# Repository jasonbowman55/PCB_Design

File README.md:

# PCB_Design

This repository will hold all of the necessary files for me to begin learning how to better design PCB boards, as well as project files for various PCB design projects.

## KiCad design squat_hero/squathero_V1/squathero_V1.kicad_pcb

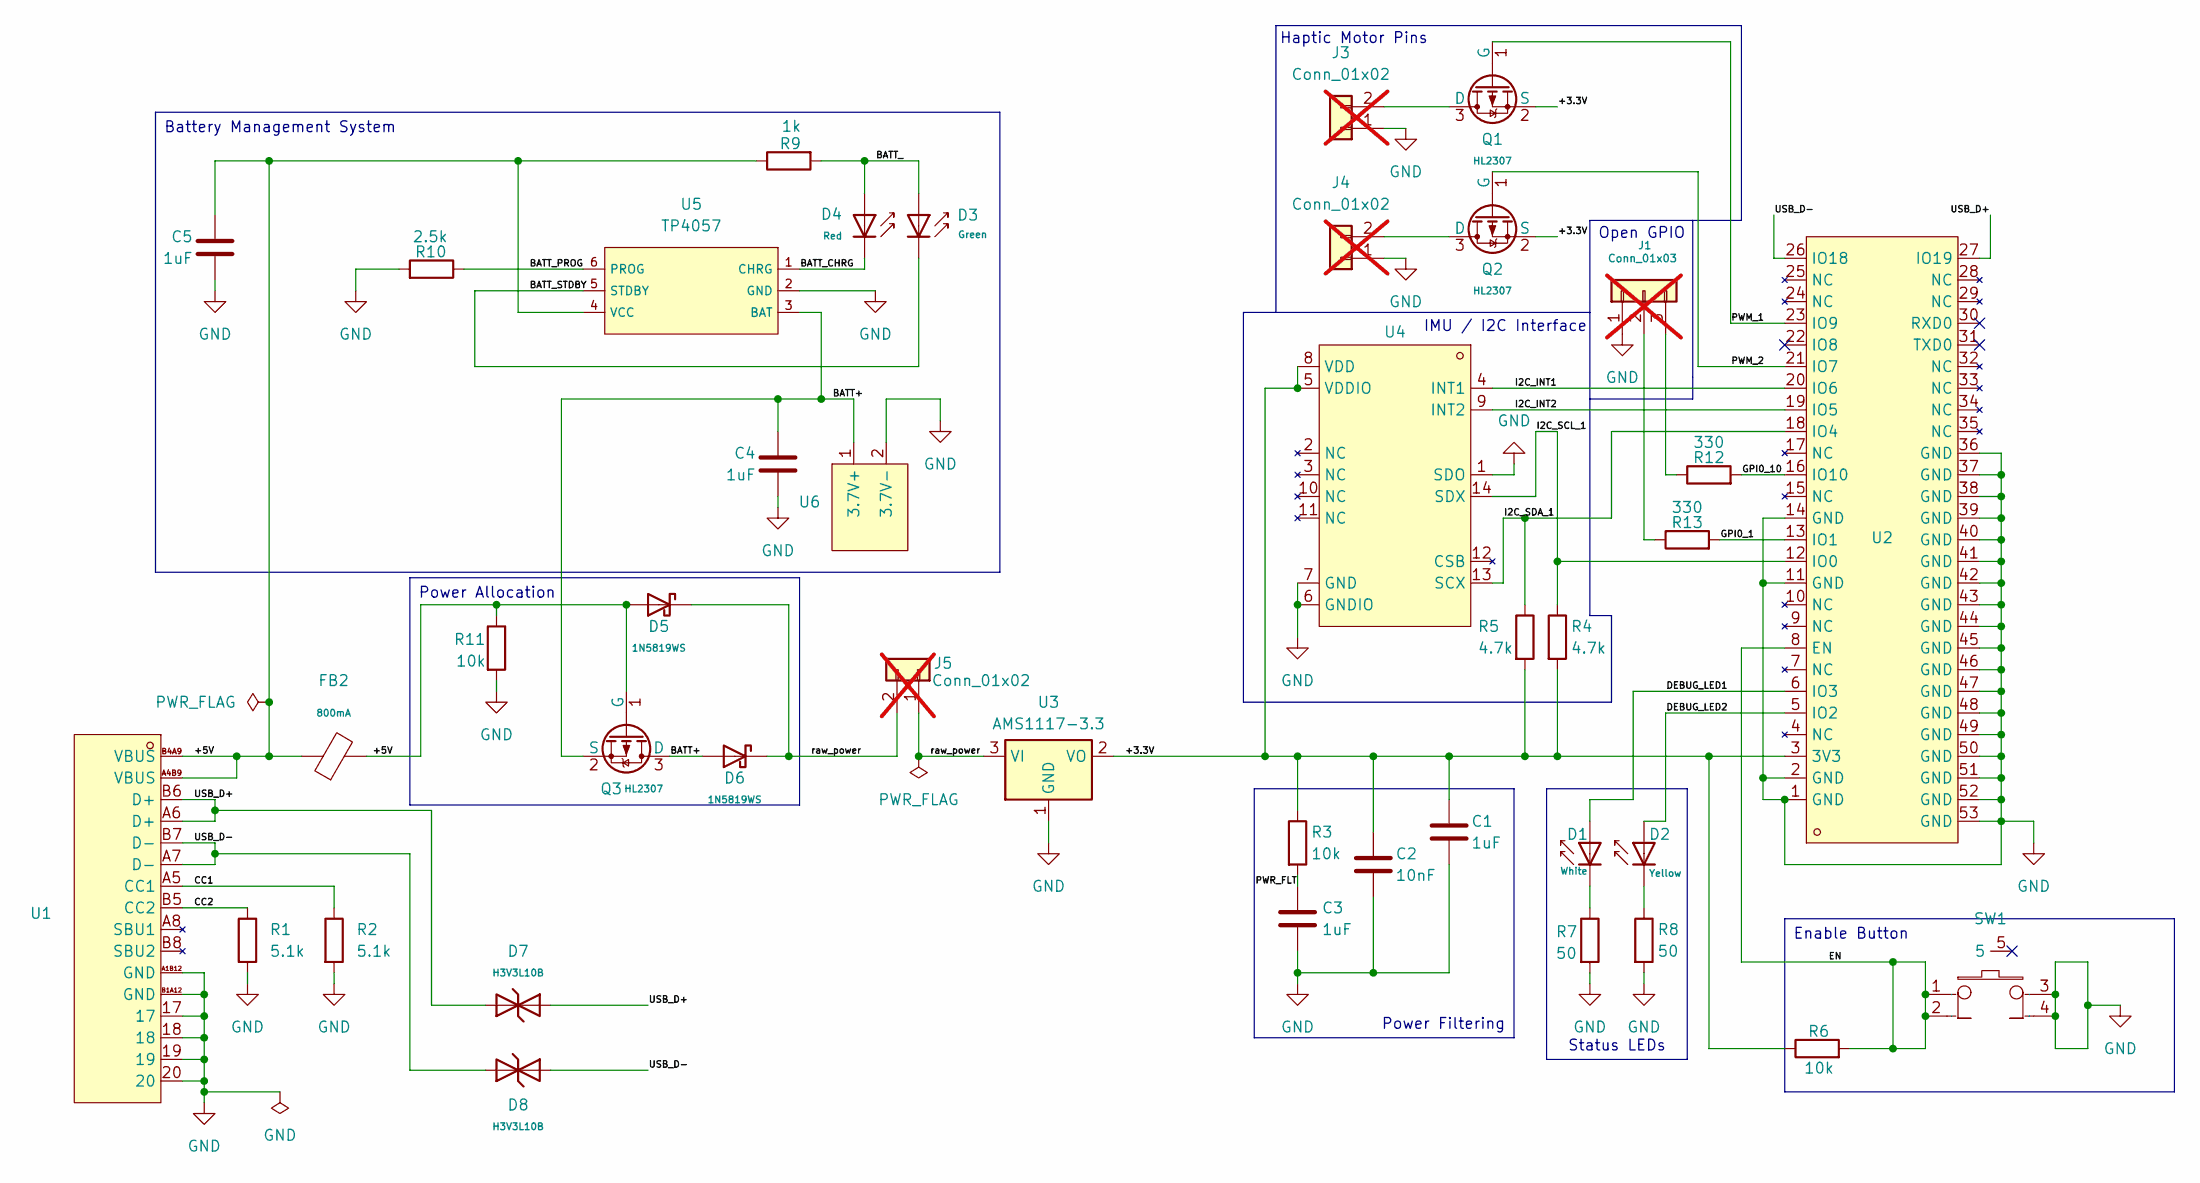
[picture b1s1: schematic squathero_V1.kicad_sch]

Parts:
C1, C3, C4, C5: 1uF; R_0805_2012Metric
C2: 10nF; R_0805_2012Metric
D1: White; D_0805; Part KT-0805W; LCSC C34499
D2: Yellow; D_0805; Part KT-0805Y; LCSC C2296
D3: Green; D_0805; Part KT-0805G; LCSC C2297
D4: Red; D_0603; Part KT-0603R; LCSC C2286
D5, D6: 1N5819WS; D_SOD-323; Forward Voltage (Vf@If) 600mV@1A; Reverse Voltage (Vr) 40V; Part 1N5819WS; LCSC C191023
D7, D8: H3V3L10B; D_DFN1006-2L; Breakdown Voltage 5.5V; Part H3V3L10B; LCSC C20615781
FB2: FB_0805; Current Rating 800mA; Tolerance ±25%; Part GZ2012D101TF; LCSC C1015
J1: Conn_01x03; PinSocket_1x03_P2.54mm_Vertical; not fitted
J3, J4, J5: Conn_01x02; PinSocket_1x02_P2.54mm_Vertical; not fitted
Q1, Q2, Q3: HL2307; Q_SOT-23; Part HL2307; LCSC C28646274
R1, R2: 5.1k; R_0603_1608Metric
R3, R6, R11: 10k; R_0805_2012Metric
R4, R5: 4.7k; R_0805_2012Metric
R7, R8: 50; R_0805_2012Metric
R9: 1k; R_0805_2012Metric
R10: 2.5k; R_0805_2012Metric
R12, R13: 330; R_0805_2012Metric
SW1: SW-SMD_4P-L3.5-W3.5_PTS840GKPSMTRLFS; Manufacturer Part PTS840GKPSMTRLFS; LCSC Part Name 轻触开关3.5mm*3.55mm，220gf
U1: USB-SMD_TYPE-C16PIN-1; Manufacturer Part 12402012E212A; LCSC Part Name Type-C 母
U2: WIFIM-SMD_ESP32-C3-MINI-1; Manufacturer Part ESP32-C3-MINI-1-N4; LCSC Part Name ESP32-C3-MINI-1-N4
U3: AMS1117-3.3; SOT-223-3_TabPin2
U4: LGA-14_L3.0-W2.5-P0.50-TL_QMI8658A; Manufacturer Part BMI323; LCSC Part Name BMI323
U5: TP4057; SOT-23-6_L2.9-W1.6-P0.95-LS2.8-BL; Part TP4057-42-SOT26-R; LCSC C12044
U6: Untitled

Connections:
/+3.3V: C1.1, C2.1, Q1.2 (S), Q2.2 (S), R3.1, R4.2, R5.2, R6.1, U2.3 (3V3), U3.2 (VO), U4.5 (VDDIO), U4.8 (VDD)
/+5V: C5.1, D5.2, FB2.1, FB2.2, Q3.1 (G), R9.1, R11.1, U1.A4B9 (VBUS), U1.B4A9 (VBUS), U5.4 (VCC)
/BATT+: C4.1, D6.2, Q3.2 (S), Q3.3 (D), U5.3 (BAT), U6.1 (3.7V+)
/BATT_: D3.2, D4.2, R9.2
/BATT_CHRG: D4.1, U5.1 (CHRG)
/BATT_PROG: R10.1, U5.6 (PROG)
/BATT_STDBY: D3.1, U5.5 (STDBY)
/CC1: R2.1, U1.A5 (CC1)
/CC2: R1.1, U1.B5 (CC2)
/DEBUG_LED1: D1.2, U2.6 (IO3)
/DEBUG_LED2: D2.2, U2.5 (IO2)
/EN: R6.2, SW1.1, SW1.2, U2.8 (EN)
/GPI0_1: R13.2, U2.13 (IO1)
/GPI0_10: R12.2, U2.16 (IO10)
/I2C_INT1: U2.20 (IO6), U4.4 (INT1)
/I2C_INT2: U2.19 (IO5), U4.9 (INT2)
/I2C_SCL_1: R4.1, U2.12 (IO0), U4.14 (SDX)
/I2C_SDA_1: R5.1, U2.18 (IO4), U4.13 (SCX)
/PWM_1: Q1.1 (G), U2.23 (IO9)
/PWM_2: Q2.1 (G), U2.21 (IO7)
/PWR_FLT: C3.1, R3.2
/USB_D+: D7.1, D7.2, U1.A6 (D+), U1.B6 (D+), U2.27 (IO19)
/USB_D-: D8.1, D8.2, U1.A7 (D-), U1.B7 (D-), U2.26 (IO18)
/raw_power: D5.1, D6.1, J5.1, J5.2, U3.3 (VI)
GND: C1.2, C2.2, C3.2, C4.2, C5.2, J1.1, J3.1, J4.1, R1.2, R2.2, R7.2, R8.2, R10.2, R11.2, SW1.3, SW1.4, U1.17, U1.18, U1.19, U1.20, U1.A1B12 (GND), U1.B1A12 (GND), U2.1 (GND), U2.2 (GND), U2.11 (GND), U2.14 (GND), U2.36 (GND), U2.37 (GND), U2.38 (GND), U2.39 (GND), U2.40 (GND), U2.41 (GND), U2.42 (GND), U2.43 (GND), U2.44 (GND), U2.45 (GND), U2.46 (GND), U2.47 (GND), U2.48 (GND), U2.49 (GND), U2.50 (GND), U2.51 (GND), U2.52 (GND), U2.53 (GND), U3.1 (GND), U4.1 (SDO), U4.6 (GNDIO), U4.7 (GND), U5.2 (GND), U6.2 (3.7V-)
unnamed: D1.1, R7.1
unnamed: D2.1, R8.1
unnamed: J1.2, R13.1
unnamed: J1.3, R12.1
unnamed: J3.2, Q1.3 (D)
unnamed: J4.2, Q2.3 (D)

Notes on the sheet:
Haptic Motor Pins
IMU / I2C Interface
Open GPIO
Battery Management System
Power Allocation
Power Filtering
Status LEDs
Enable Button

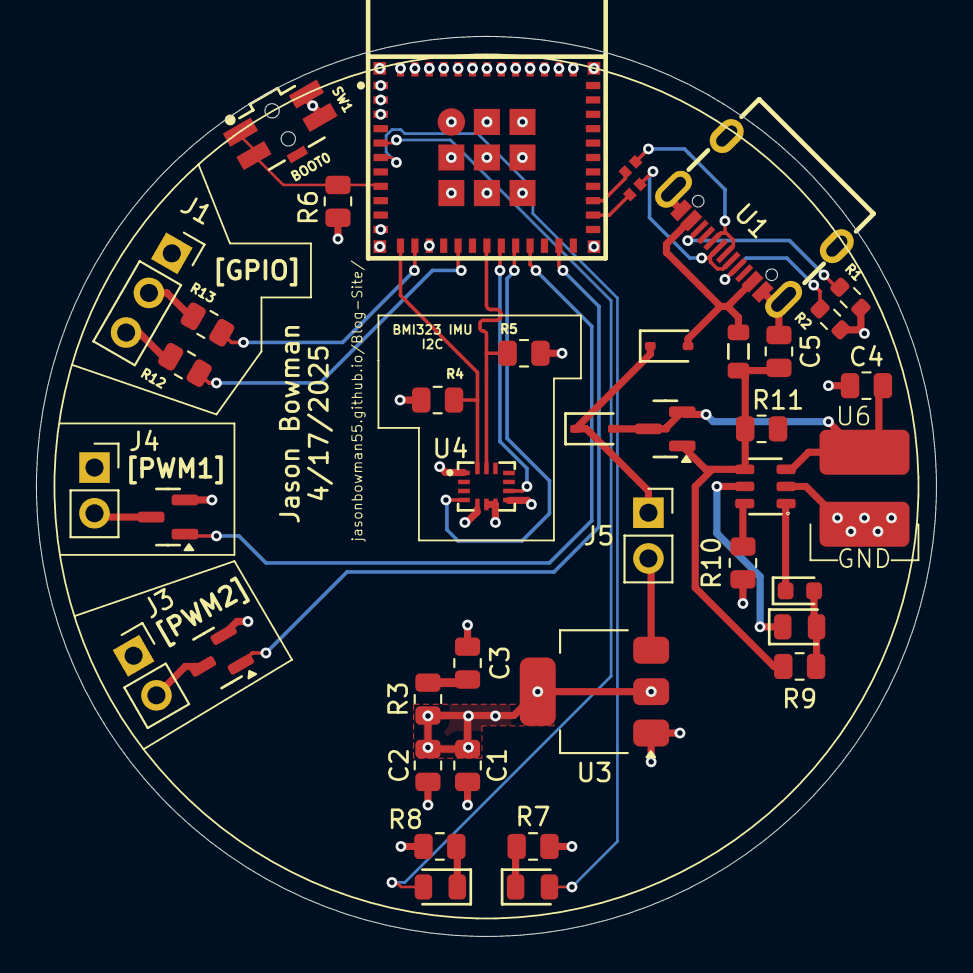
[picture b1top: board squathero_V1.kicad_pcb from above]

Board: 4 copper layers, 50.0 x 50.0 mm, 41 parts (0 on the bottom side), 31 nets.

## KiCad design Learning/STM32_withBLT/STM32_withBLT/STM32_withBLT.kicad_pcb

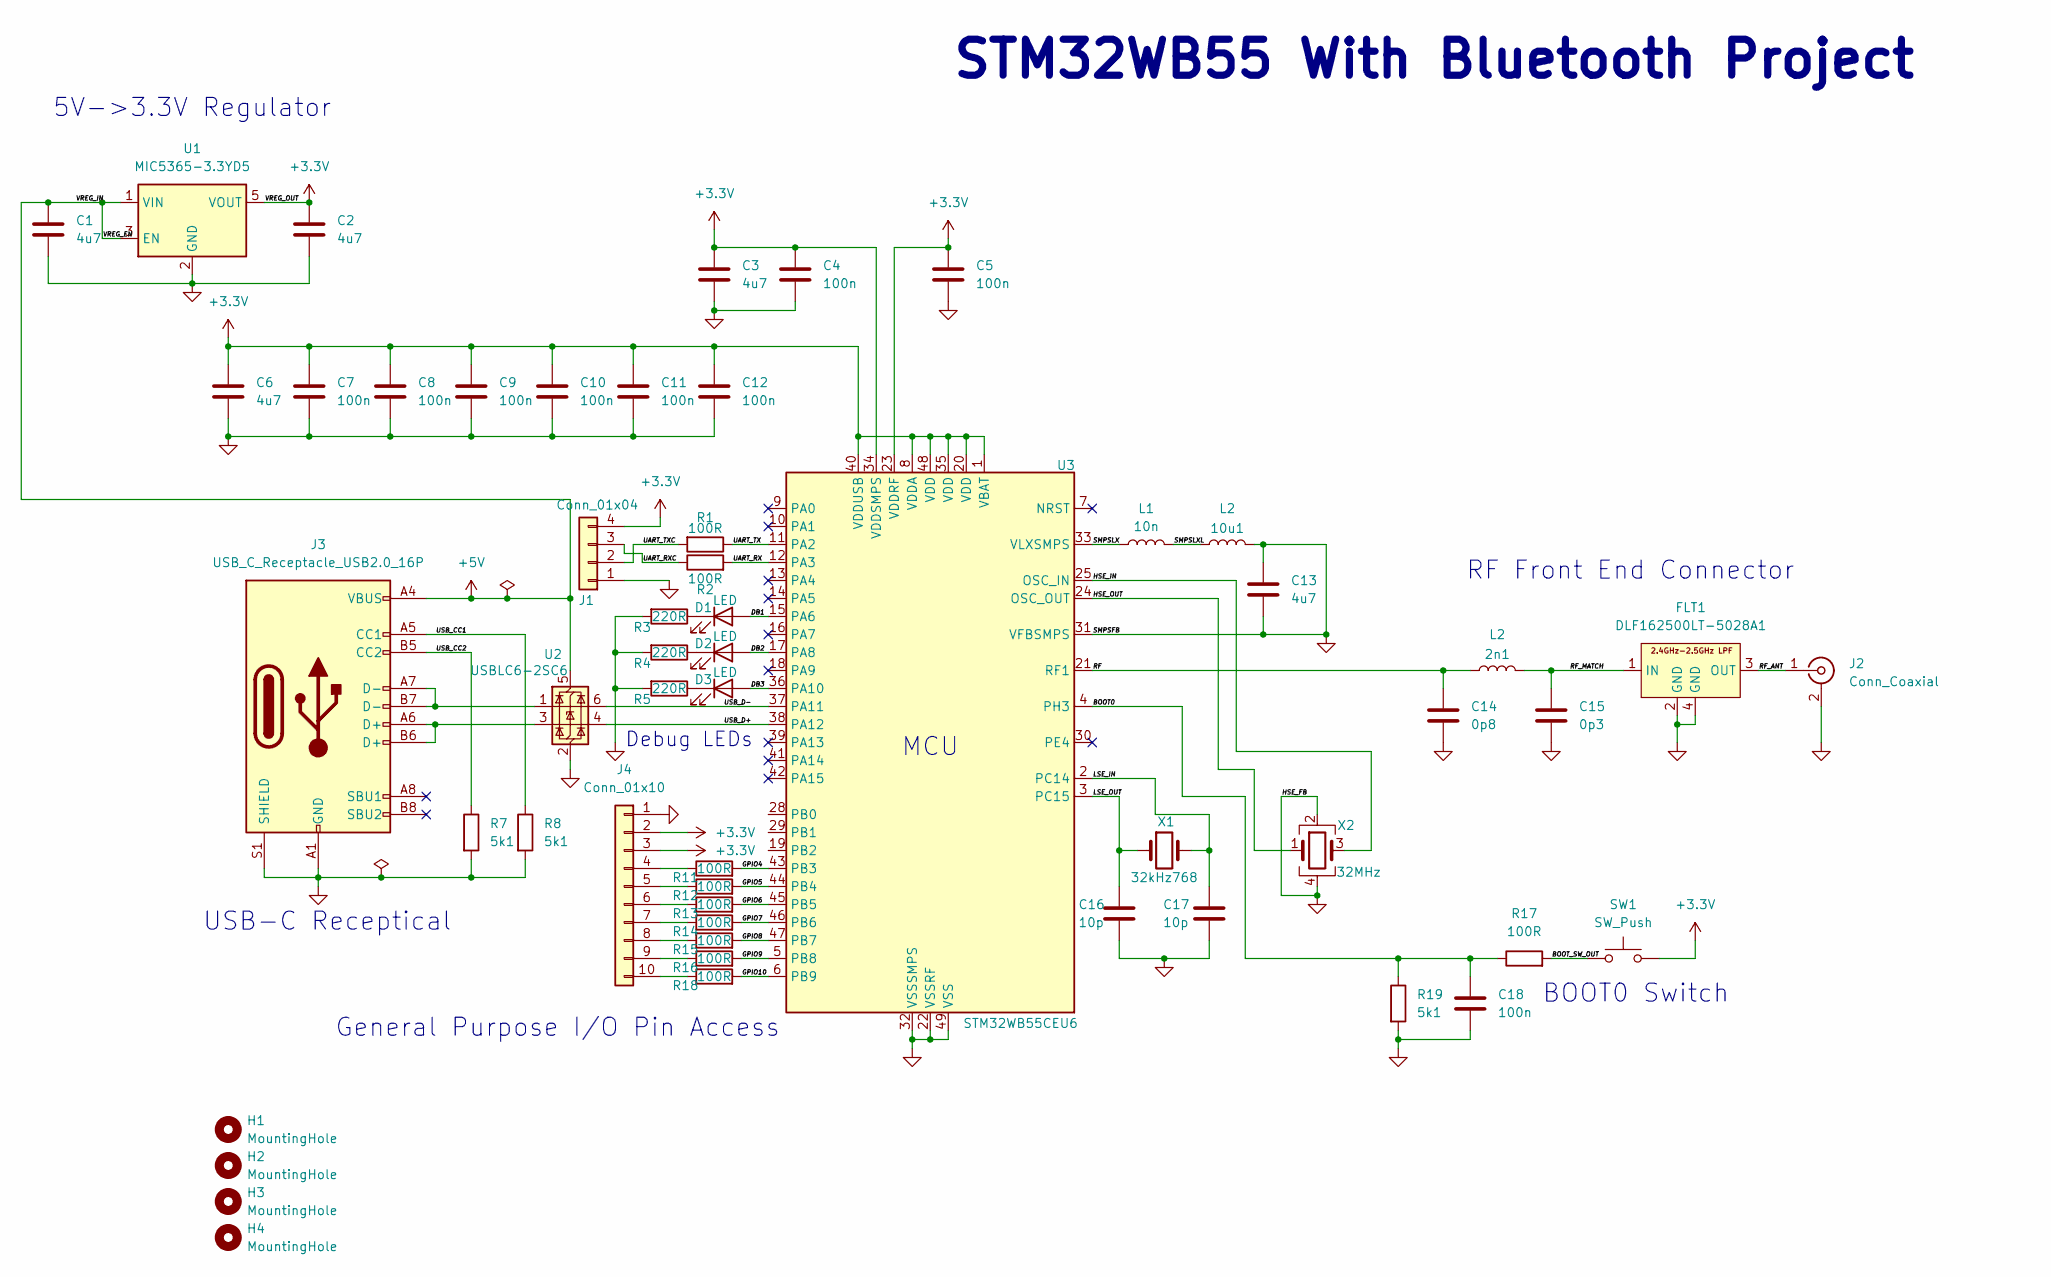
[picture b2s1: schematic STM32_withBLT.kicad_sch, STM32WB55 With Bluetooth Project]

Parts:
2n1: L2; C_0402_1005Metric
10u1: L2; C_0805_2012Metric
C1, C6: 4u7; C_0201_0603Metric
C2, C3, C13: 4u7; C_0402_1005Metric
C4, C5, C7, C8, C9, C10, C12, C18: 100n; C_0402_1005Metric
C11: 100n; C_0201_0603Metric
C14: 0p8; C_0402_1005Metric
C15: 0p3; C_0402_1005Metric
C16, C17: 10p; C_0402_1005Metric
D1, D2, D3: LED; C_0402_1005Metric
FLT1: DLF162500LT-5028A1
H1, H2, H3, H4: MountingHole; MountingHole_3.2mm_M3_Pad
J1: Conn_01x04; PinHeader_1x04_P2.54mm_Vertical
J2: Conn_Coaxial; U.FL_Hirose_U.FL-R-SMT-1_Vertical
J3: USB_C_Receptacle_USB2.0_16P; USB_C_Receptacle_GCT_USB4105-xx-A_16P_TopMnt_Horizontal
J4: Conn_01x10; PinHeader_1x10_P2.54mm_Vertical
L1: 10n; C_0402_1005Metric
R1, R2, R11, R12, R13, R14, R15, R16, R17, R18: 100R; C_0402_1005Metric
R3, R4, R5: 220R; C_0402_1005Metric
R7, R8, R19: 5k1; C_0402_1005Metric
SW1: SW_Push; SW_SPST_FSMSM
U1: MIC5365-3.3YD5; SOT-23-5
U2: USBLC6-2SC6; SOT-23-6
U3: STM32WB55CEU6; QFN-48-1EP_7x7mm_P0.5mm_EP5.6x5.6mm
X1: 32kHz768; Crystal_SMD_2012-2Pin_2.0x1.2mm
X2: 32MHz; Crystal_SMD_2016-4Pin_2.0x1.6mm

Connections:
+3.3V: C2.1, C3.1, C4.1, C5.1, C6.1, C7.1, C8.1, C9.1, C10.1, C11.1, C12.1, J1.4, J4.2, J4.3, SW1.2, U1.5 (VOUT), U3.1 (VBAT), U3.8 (VDDA), U3.20 (VDD), U3.23 (VDDRF), U3.34 (VDDSMPS), U3.35 (VDD), U3.40 (VDDUSB), U3.48 (VDD)
+5V: C1.1, J3.A4 (VBUS), J3.A9 (VBUS), J3.B4 (VBUS), J3.B9 (VBUS), U1.1 (VIN), U1.3 (EN), U2.5 (VBUS)
/BOOT0: C18.1, R17.1, R19.1, U3.4 (PH3)
/BOOT_SW_OUT: R17.2, SW1.1
/DB1: D1.2 (A), U3.15 (PA6)
/DB2: D2.2 (A), U3.17 (PA8)
/DB3: D3.2 (A), U3.36 (PA10)
/GPIO4: R11.2, U3.43 (PB3)
/GPIO5: R12.2, U3.44 (PB4)
/GPIO6: R13.2, U3.45 (PB5)
/GPIO7: R14.2, U3.46 (PB6)
/GPIO8: R15.2, U3.47 (PB7)
/GPIO9: R16.2, U3.5 (PB8)
/GPIO10: R18.2, U3.6 (PB9)
/HSE_IN: U3.25 (OSC_IN), X2.3
/HSE_OUT: U3.24 (OSC_OUT), X2.1
/LSE_IN: C17.1, U3.2 (PC14), X1.2
/LSE_OUT: C16.1, U3.3 (PC15), X1.1
/RF: 2n1.1, C14.1, U3.21 (RF1)
/RF_ANT: FLT1.3 (OUT), J2.1 (In)
/RF_MATCH: 2n1.2, C15.1, FLT1.1 (IN)
/SMPSLX: L1.1, U3.33 (VLXSMPS)
/SMPSLXL: 10u1.1, L1.2
/UART_RX: R2.2, U3.12 (PA3)
/UART_RXC: J1.3, R2.1
/UART_TX: R1.1, U3.11 (PA2)
/UART_TXC: J1.2, R1.2
/USB_CC1: J3.A5 (CC1), R8.1
/USB_CC2: J3.B5 (CC2), R7.1
/USB_D+: U2.4 (I/O2), U3.38 (PA12)
/USB_D-: U2.6 (I/O1), U3.37 (PA11)
GND: 10u1.2, C1.2, C2.2, C3.2, C4.2, C5.2, C6.2, C7.2, C8.2, C9.2, C10.2, C11.2, C12.2, C13.1, C13.2, C14.2, C15.2, C16.2, C17.2, C18.2, FLT1.2 (GND), FLT1.4 (GND), J1.1, J2.2 (Ext), J3.A1 (GND), J3.A12 (GND), J3.B1 (GND), J3.B12 (GND), J3.S1 (SHIELD), J4.1, R3.2, R4.2, R5.2, R7.2, R8.2, R19.2, U1.2 (GND), U2.2 (GND), U3.22 (VSSRF), U3.31 (VFBSMPS), U3.32 (VSSSMPS), U3.49 (VSS), X2.2, X2.4
unnamed: D1.1 (K), R3.1
unnamed: D2.1 (K), R4.1
unnamed: D3.1 (K), R5.1
unnamed: J3.A6 (D+), J3.B6 (D+), U2.3 (I/O2)
unnamed: J3.A7 (D-), J3.B7 (D-), U2.1 (I/O1)
unnamed: J4.4, R11.1
unnamed: J4.5, R12.1
unnamed: J4.6, R13.1
unnamed: J4.7, R14.1
unnamed: J4.8, R15.1
unnamed: J4.9, R16.1
unnamed: J4.10, R18.1

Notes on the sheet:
Debug LEDs
STM32WB55 With Bluetooth Project
General Purpose I/O Pin Access
RF Front End Connector
USB-C Receptical
5V->3.3V Regulator
MCU
BOOT0 Switch

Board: 4 copper layers, 55 parts (0 on the bottom side), 44 nets, no tracks yet.

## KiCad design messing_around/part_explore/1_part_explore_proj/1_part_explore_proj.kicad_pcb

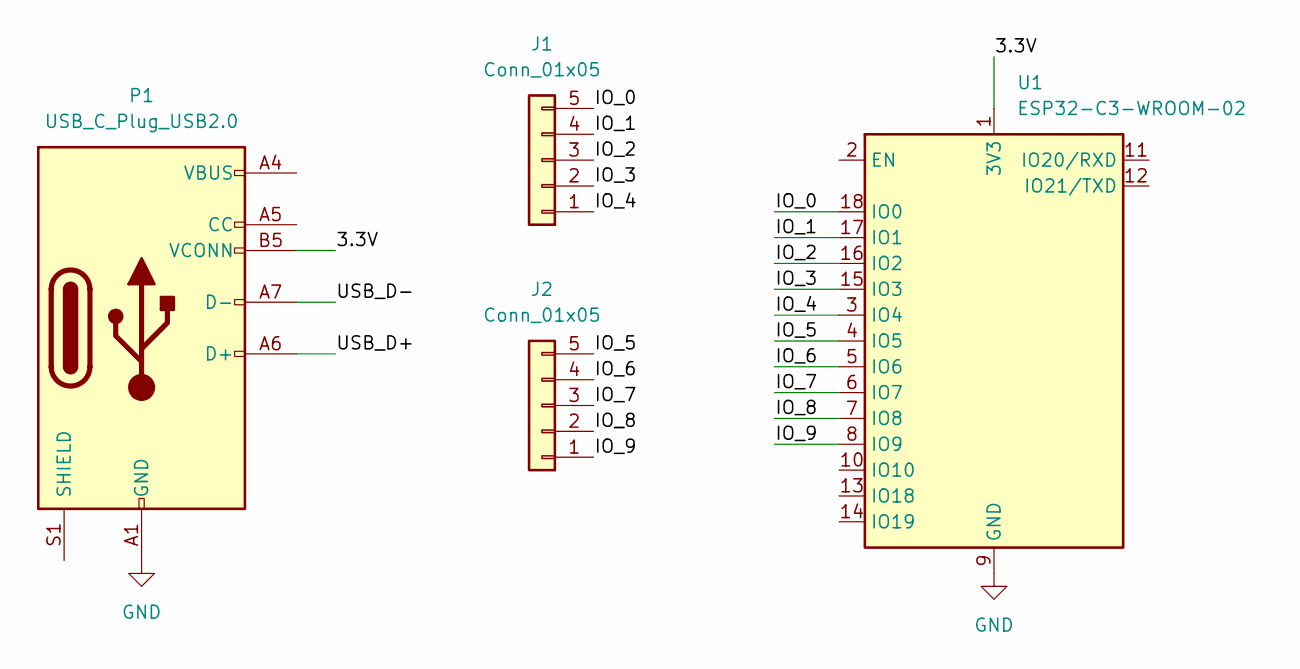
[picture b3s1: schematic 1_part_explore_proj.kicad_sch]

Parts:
J1, J2: Conn_01x05; PinHeader_1x05_P1.00mm_Vertical
P1: USB_C_Plug_USB2.0; USB_C_Receptacle_HRO_TYPE-C-31-M-12
U1: ESP32-C3-WROOM-02

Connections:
/3.3V: P1.B5 (VCONN), U1.1 (3V3)
/IO_0: J1.5, U1.18 (IO0)
/IO_1: J1.4, U1.17 (IO1)
/IO_2: J1.3, U1.16 (IO2)
/IO_3: J1.2, U1.15 (IO3)
/IO_4: J1.1, U1.3 (IO4)
/IO_5: J2.5, U1.4 (IO5)
/IO_6: J2.4, U1.5 (IO6)
/IO_7: J2.3, U1.6 (IO7)
/IO_8: J2.2, U1.7 (IO8)
/IO_9: J2.1, U1.8 (IO9)
/USB_D+: P1.A6 (D+)
/USB_D-: P1.A7 (D-)
GND: P1.A1 (GND), P1.A12 (GND), P1.B1 (GND), P1.B12 (GND), U1.9 (GND), U1.19 (GND)
unnamed: P1.A4 (VBUS), P1.A9 (VBUS), P1.B4 (VBUS), P1.B9 (VBUS)

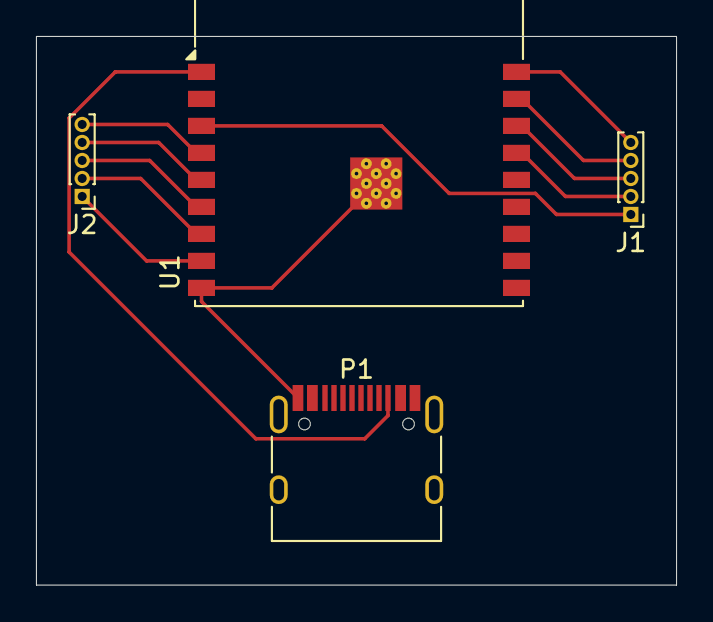
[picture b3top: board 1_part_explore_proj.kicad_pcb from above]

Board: 2 copper layers, 35.6 x 30.5 mm, 4 parts (0 on the bottom side), 13 nets.

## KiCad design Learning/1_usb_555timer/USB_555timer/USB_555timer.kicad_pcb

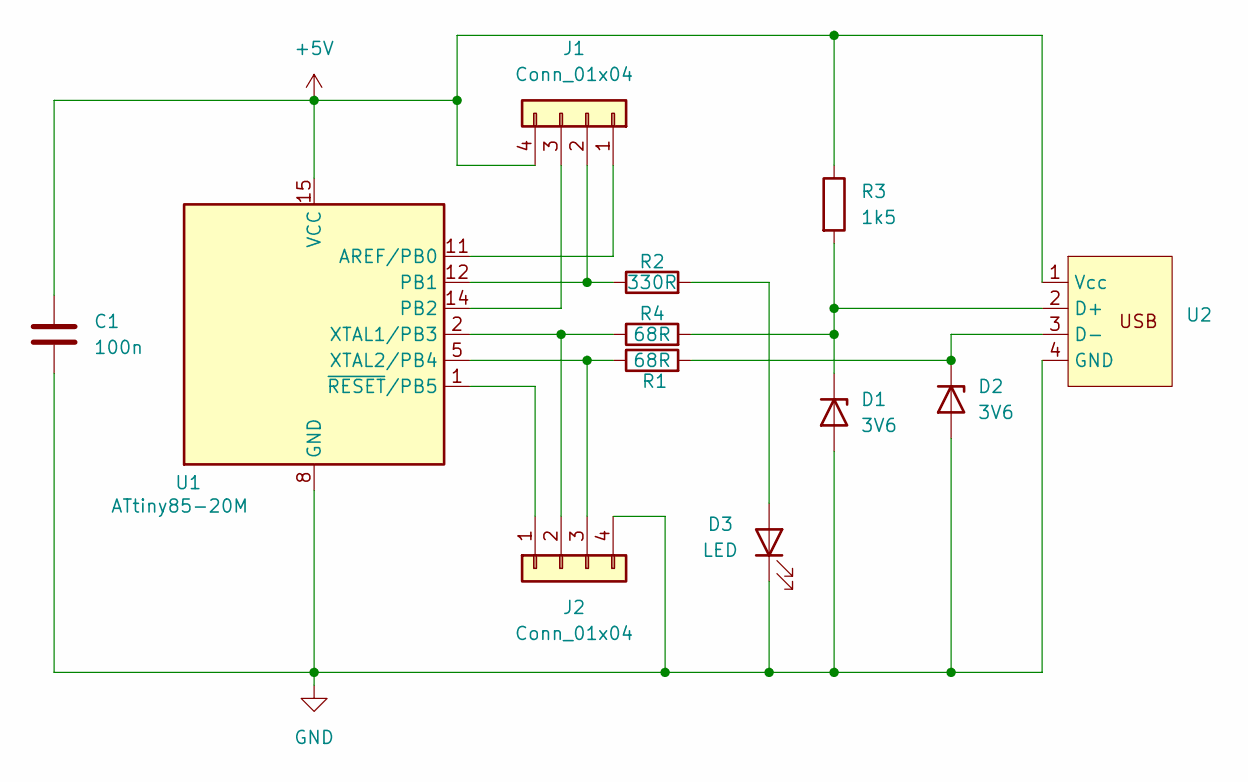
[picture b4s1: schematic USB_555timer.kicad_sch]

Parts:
C1: 100n; C_1206_3216Metric_Pad1.33x1.80mm_HandSolder
D1, D2: 3V6; D_SOD-123
D3: LED; C_1206_3216Metric_Pad1.33x1.80mm_HandSolder
J1, J2: Conn_01x04; SolderWire-0.1sqmm_1x04_P3.6mm_D0.4mm_OD1mm
R1, R4: 68R; R_0805_2012Metric_Pad1.20x1.40mm_HandSolder
R2: 330R; R_0805_2012Metric_Pad1.20x1.40mm_HandSolder
R3: 1k5; R_0805_2012Metric_Pad1.20x1.40mm_HandSolder
U1: ATtiny85-20M; QFN-20-1EP_4x4mm_P0.5mm_EP2.6x2.6mm
U2: PCB_USB_connector

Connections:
+5V: C1.1, J1.4, R3.1, U1.15 (VCC), U2.1 (Vcc)
GND: C1.2, D1.2 (A), D2.2 (A), D3.1 (K), J2.4, U1.8 (GND), U1.21 (GND), U2.4 (GND)
unnamed: D1.1 (K), R3.2, R4.2, U2.2 (D+)
unnamed: D2.1 (K), R1.2, U2.3 (D-)
unnamed: D3.2 (A), R2.2
unnamed: J1.1, U1.11 (AREF/PB0)
unnamed: J1.2, R2.1, U1.12 (PB1)
unnamed: J1.3, U1.14 (PB2)
unnamed: J2.1, U1.1 (~RESET/PB5)
unnamed: J2.2, R4.1, U1.2 (XTAL1/PB3)
unnamed: J2.3, R1.1, U1.5 (XTAL2/PB4)

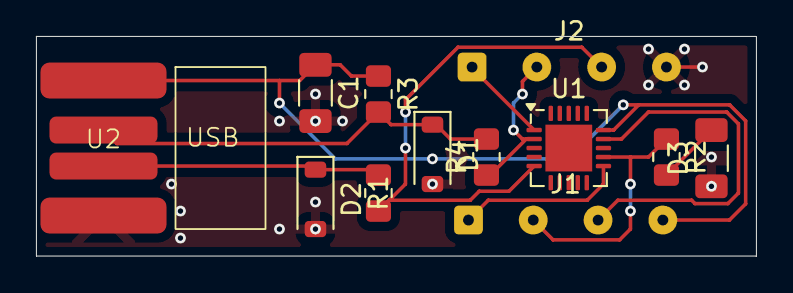
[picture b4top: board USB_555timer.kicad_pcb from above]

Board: 2 copper layers, 40.0 x 12.2 mm, 12 parts (0 on the bottom side), 11 nets.

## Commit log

2025-02-19 USB Stick Done
2025-02-21 messing around
2025-02-26 messing around with the settings
2025-02-26 finished STM32 w/ BT schematic
2025-03-03 added my own peripherals
2025-03-17 update from laptop
2025-04-04 initial stm32 bt pcb layout
2025-04-04 stm32 initial pcb layoout
2025-04-04 test
2025-04-08 random
2025-04-08 squat_hero_V1: USB interface complete
2025-04-08 library localization
2025-04-18 V1 squat hero
2025-04-18 all formatted besides power / BMS
